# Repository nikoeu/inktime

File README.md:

# Proiect Smartwatch - Documentație Hardware

## 1. Diagramă Bloc

Mai jos este prezentată arhitectura sistemului și modul în care comunică principalele module:

    +-------------------+
    |                   |
    |   BQ25180YBGR     | <==== I2C ====> 
    | (PMIC & Charger)  |                 |
    |                   | --- VREG 3.3V --+
    +-------------------+                 |
                                          |
    +-------------------+                 v
    |                   |
    |                   | <==== I2C ====> IMU (Accel/Gyro)
    |     nRF52840      |
    |  (SoC Principal)  | <==== SPI ====> Ecran E-Paper (EPD)
    |                   |
    |                   | ==== GPIO ====> Driver / Motor Haptic
    +-------------------+

**Conexiuni principale:**

* **Alimentare:** Port USB-C ➜ BQ25180 (PMIC) ➜ Baterie Li-Po & VREG (3.3V System Power). MCU-ul se alimentează din pinul VREG.
* **Periferice I2C:** PMIC-ul (Control/Status) și IMU-ul împart aceeași magistrală I2C.
* **Periferice SPI:** E-Paper Display (EPD) este conectat pe magistrala SPI dedicată.
* **I/O Adițional:** 3 Butoane tactile, Interfața SWD pentru programare și controlul motorului haptic.

## 2. Bill of Materials (BOM)

Tabelul de mai jos conține modulele și componentele principale folosite în designul PCB-ului. Din considerente de formatare pentru recenzie, link-urile directe au fost omise, componentele fiind disponibile standard în catalogul JLC Parts.

| Componentă / Modul | Rol în sistem | Sursă | Documentație |
|---|---|---|---|
| **nRF52840** | Microcontroler principal (BGA) cu BLE | JLC Parts | Datasheet Producător |
| **BQ25180YBGR** | PMIC / Încărcător baterie Li-Po | JLC Parts | Datasheet Producător |
| **LSM6DS3 / MPU6050** | Senzor de mișcare (IMU - Accel/Giroscop) | JLC Parts | Datasheet Producător |
| **Modul EPD SPI** | Conector și suport pentru ecranul E-Paper | JLC Parts | Datasheet Producător |
| **Modul Haptic** | Driver / Motor Vibrații pentru feedback tactil | JLC Parts | Datasheet Producător |
| **Conector USB-C** | Intrare alimentare (VBUS) | JLC Parts | Datasheet Producător |
| **Butoane Tactile SMD** | Interacțiune utilizator (GND pe apăsare) | JLC Parts | Datasheet Producător |

## 3. Descrierea Funcționalității Hardware

Sistemul hardware este proiectat în jurul SoC-ului **nRF52840**, ales pentru capabilitățile sale excelente de Bluetooth Low Energy (BLE) și consumul redus, ideal pentru un dispozitiv purtabil.

* **Managementul Puterii (PMIC):** Am folosit integratul **BQ25180**, un PMIC și încărcător liniar extrem de compact. Acesta preia tensiunea de 5V din portul USB (VBUS), gestionează încărcarea sigură a bateriei (VBAT) și furnizează o tensiune stabilizată sistemului prin pinul VREG/SYS (stabilită la 3.3V). Comunicația cu MCU-ul se face prin magistrala I2C pentru a citi starea bateriei și a configura curentul de încărcare.
* **Interfața cu utilizatorul:** Afișajul este realizat printr-un ecran E-Paper, conectat via magistrala **SPI**. Acest tip de display a fost ales datorită consumului zero de energie pentru reținerea imaginii (esențial pentru autonomia unui ceas). Navigarea se face prin 3 butoane fizice (active low), iar feedback-ul tactil este asigurat de un modul haptic.
* **Senzoristică:** Modulul IMU comunică cu MCU-ul tot prin interfața **I2C** (partajată cu PMIC-ul) și dispune de pini de întrerupere hardware (INT1/INT2) pentru a "trezi" microcontrolerul doar la detectarea mișcării (ex: ridicarea mâinii), economisind astfel baterie.
* **Consum:** În mod *Deep Sleep*, consumul microcontrolerului împreună cu PMIC-ul este de ordinul microamperilor (uA). La activarea BLE și a ecranului (refresh), consumul crește temporar. Sistemul este proiectat astfel încât perifericele să poată fi adormite sau oprite independent.

## 4. Maparea Pinilor nRF52840

Pinii au fost aleși strategic pentru a optimiza rutarea pe PCB sub pachetul BGA, evitând pe cât posibil intersecțiile majore.

| Pin / Label | Funcție asociată | Justificare / Protocol |
|---|---|---|
| **SDA / SCL** | I2C Data & Clock | Magistrala I2C principală. Conectează MCU la BQ25180 și la IMU. |
| **EPD_CS** | Chip Select (Ecran) | Controlează activarea comunicării SPI cu ecranul E-Paper. |
| **EPD_DC** | Data / Command (Ecran) | Indică ecranului dacă datele trimise pe SPI sunt setări sau pixeli. |
| **EPD_RST** | Reset (Ecran) | Reset hardware dedicat pentru inițializarea display-ului. |
| **EPD_BUSY** | Busy State (Ecran) | Intrare în MCU; previne trimiterea de date noi în timp ce ecranul face refresh. |
| **IMU_INT1 / INT2** | Întreruperi Senzor | Trezesc MCU-ul din starea de sleep la detectarea mișcării. |
| **PMIC_INT** | Întrerupere Baterie | Alertează MCU-ul la conectarea cablului USB sau low-battery. |
| **HAPTIC_EN** | Enable Vibrații | Pin GPIO/PWM pentru controlul duratei și intensității vibrațiilor. |
| **RESET** | System Reset | Conectat la pad-urile de test (TP) pentru depanare via SWD. |
| **SWDIO / SWDCLK** | Interfață Programare | Pini dedicați pentru programarea și depanarea nRF52840. |

## 5. Jurnal de Design (Decizii, Probleme și Compromisuri)

Rutarea acestui PCB a reprezentat o provocare majoră din cauza densității mari de componente specifice unui smartwatch și a pachetului BGA al microcontrolerului. Următoarele decizii tehnice au fost luate și asumate pentru a asigura un design funcțional:

1. **Tranziția la un Stack-up cu 4 Straturi (4-Layer PCB):**
   * Datorită aglomerării extreme de pe stratul Top și a numărului mare de airwires rezultate din constrângerile mecanice, am decis utilizarea a 4 straturi.
   * **Layer 2 (Inner 1)** a fost transformat integral într-un plan de masă solid (**GND Polygon Pour**), asigurând ecranare electromagnetică și trasee de întoarcere scurte.
   * **Layer 15 (Inner 2)** a fost utilizat ca plan de alimentare (**3V3 / VREG**), curățând placa de necesitatea rutării zecilor de fire de putere.

2. **Compromisuri acceptate în DRC (Via-in-Pad și Overlap):**
   * **Problemă:** Pinii interni ai microcontrolerului nRF52840 (BGA) erau imposibil de rutat folosind tehnica tradițională ("dog-bone"), spațiul dintre pini fiind insuficient.
   * **Soluție:** Am apelat la tehnica **Via-in-Pad** (Drill: 0.15mm, Annular Ring: 0.075mm pentru a atinge diametrul total de 0.3mm acceptat de fabrica JLC).
   * **Decizie Asumată:** Am acceptat și aprobat manual erorile de tip *Clearance* și *Overlap* generate de soft pe pad-urile BGA-ului, acestea fiind o consecință intenționată (aprobată în prealabil) a utilizării tehnicii Via-in-Pad.

3. **Rutarea firelor de putere prin Vias:**
   * Deși bunele practici recomandă ca traseele de putere principale să fie menținute pe un singur strat continuu pentru a evita rezistența parazită, **am fost nevoit să trag 3 cabluri de putere (grosime 0.3mm) prin vias** pe straturile inferioare. Aglomerarea fizică din jurul zonei PMIC-ului și conectorului USB nu a permis altă soluție de escape routing exclusiv pe stratul TOP.

4. **Amplasarea Antenei (Zona de Restrict):**
   * Antena Bluetooth a fost plasată pe marginea PCB-ului conform cerințelor. Am desenat un decupaj specific în conturul plăcii (Board Outline) și am aplicat reguli de *Keepout* (excludere a poligoanelor de cupru) pe toate cele 4 straturi sub corpul antenei, interzicând rutarea semnalelor pe dedesubt pentru a respecta normele de design RF.

## 6. Limitări curente / Stadiul proiectului

* Designul PCB este complet rutat și trece verificările mecanice principale.
* **Componentă lipsă:** Datorită focusului pe rezolvarea constrângerilor complexe de rutare hardware (BGA + densitate mare de componente) și a timpului alocat asamblării cablajului, **partea de modelare 3D (designul carcasei smartwatch-ului) nu a fost realizată** în acest stadiu al proiectului.

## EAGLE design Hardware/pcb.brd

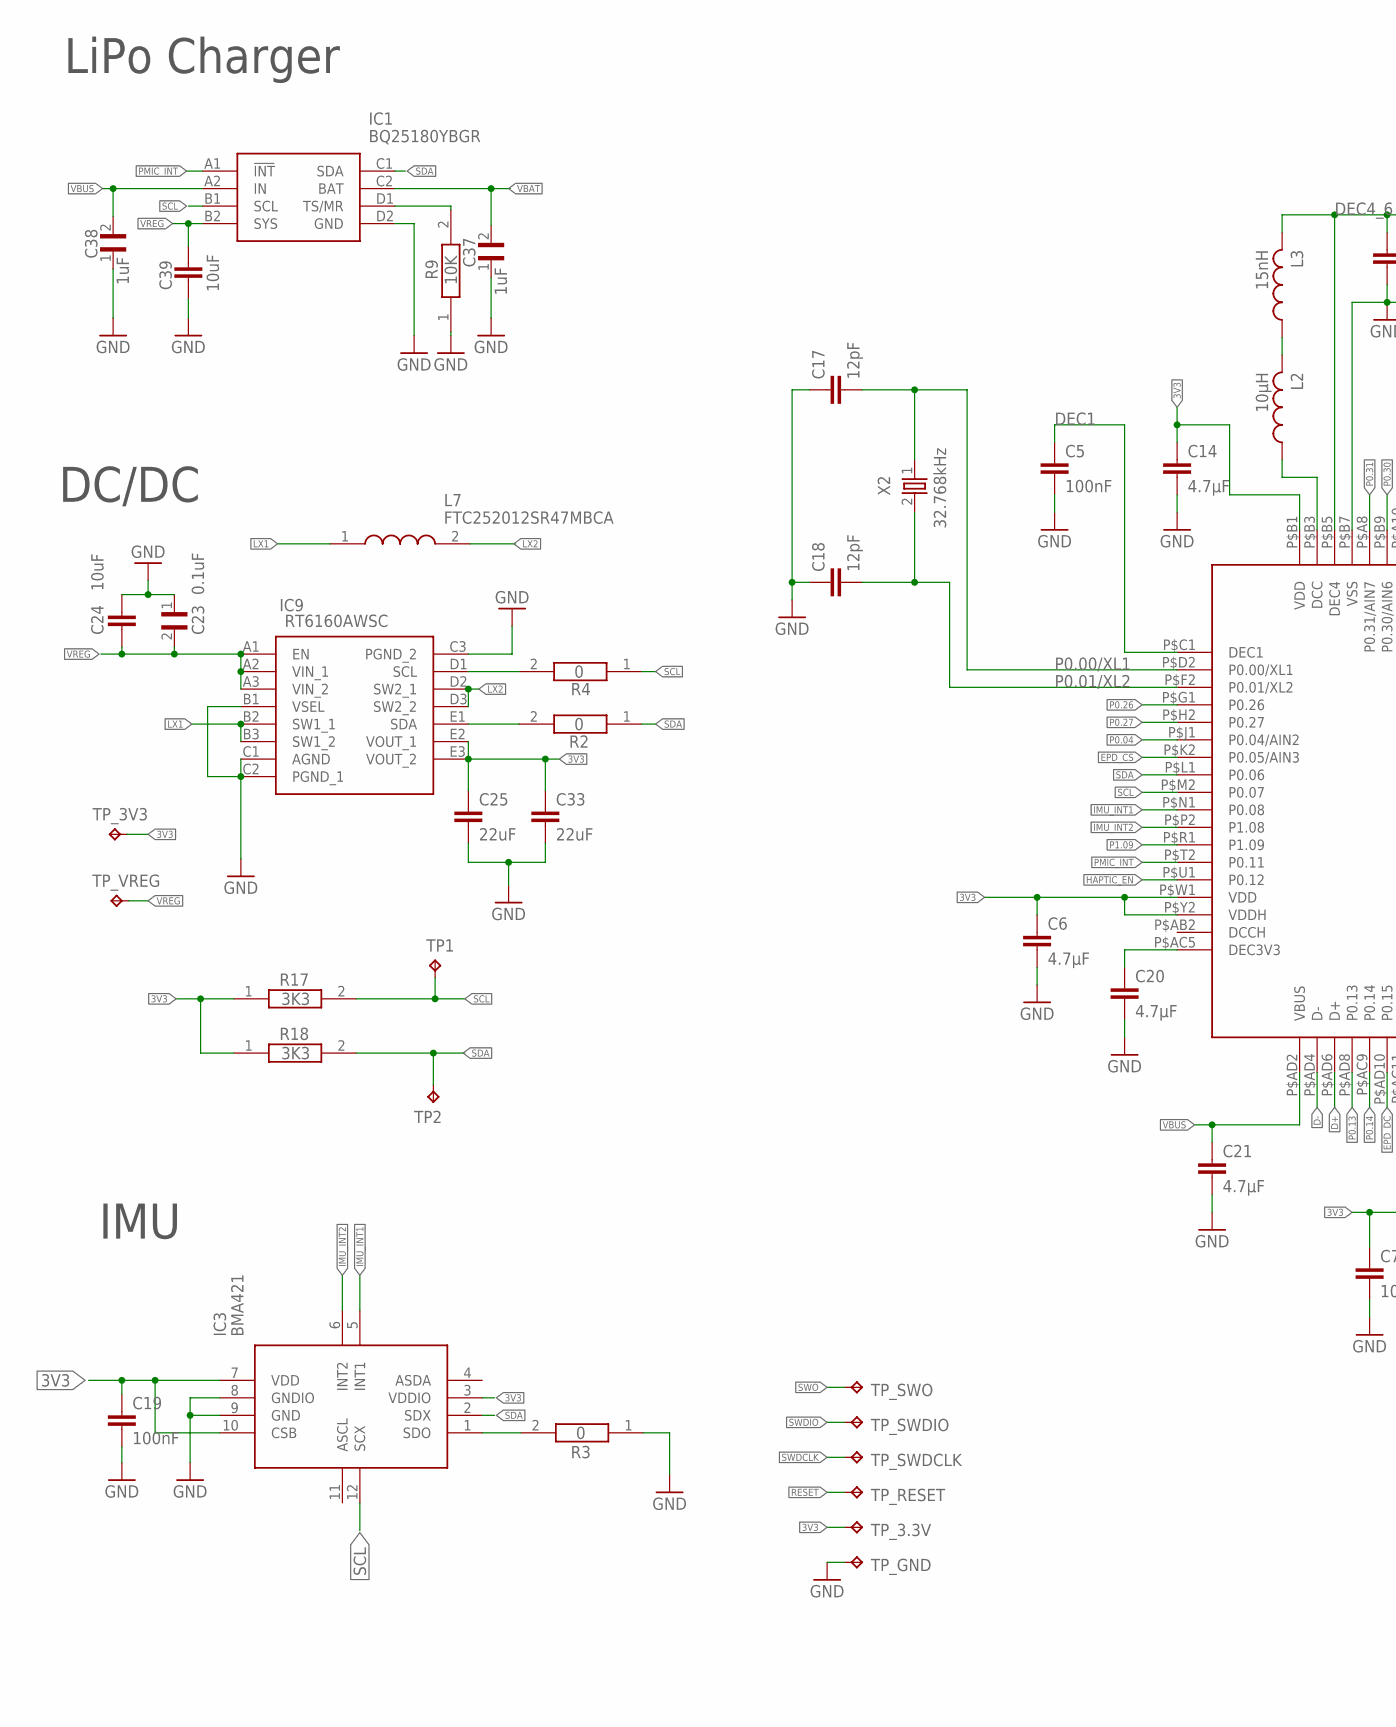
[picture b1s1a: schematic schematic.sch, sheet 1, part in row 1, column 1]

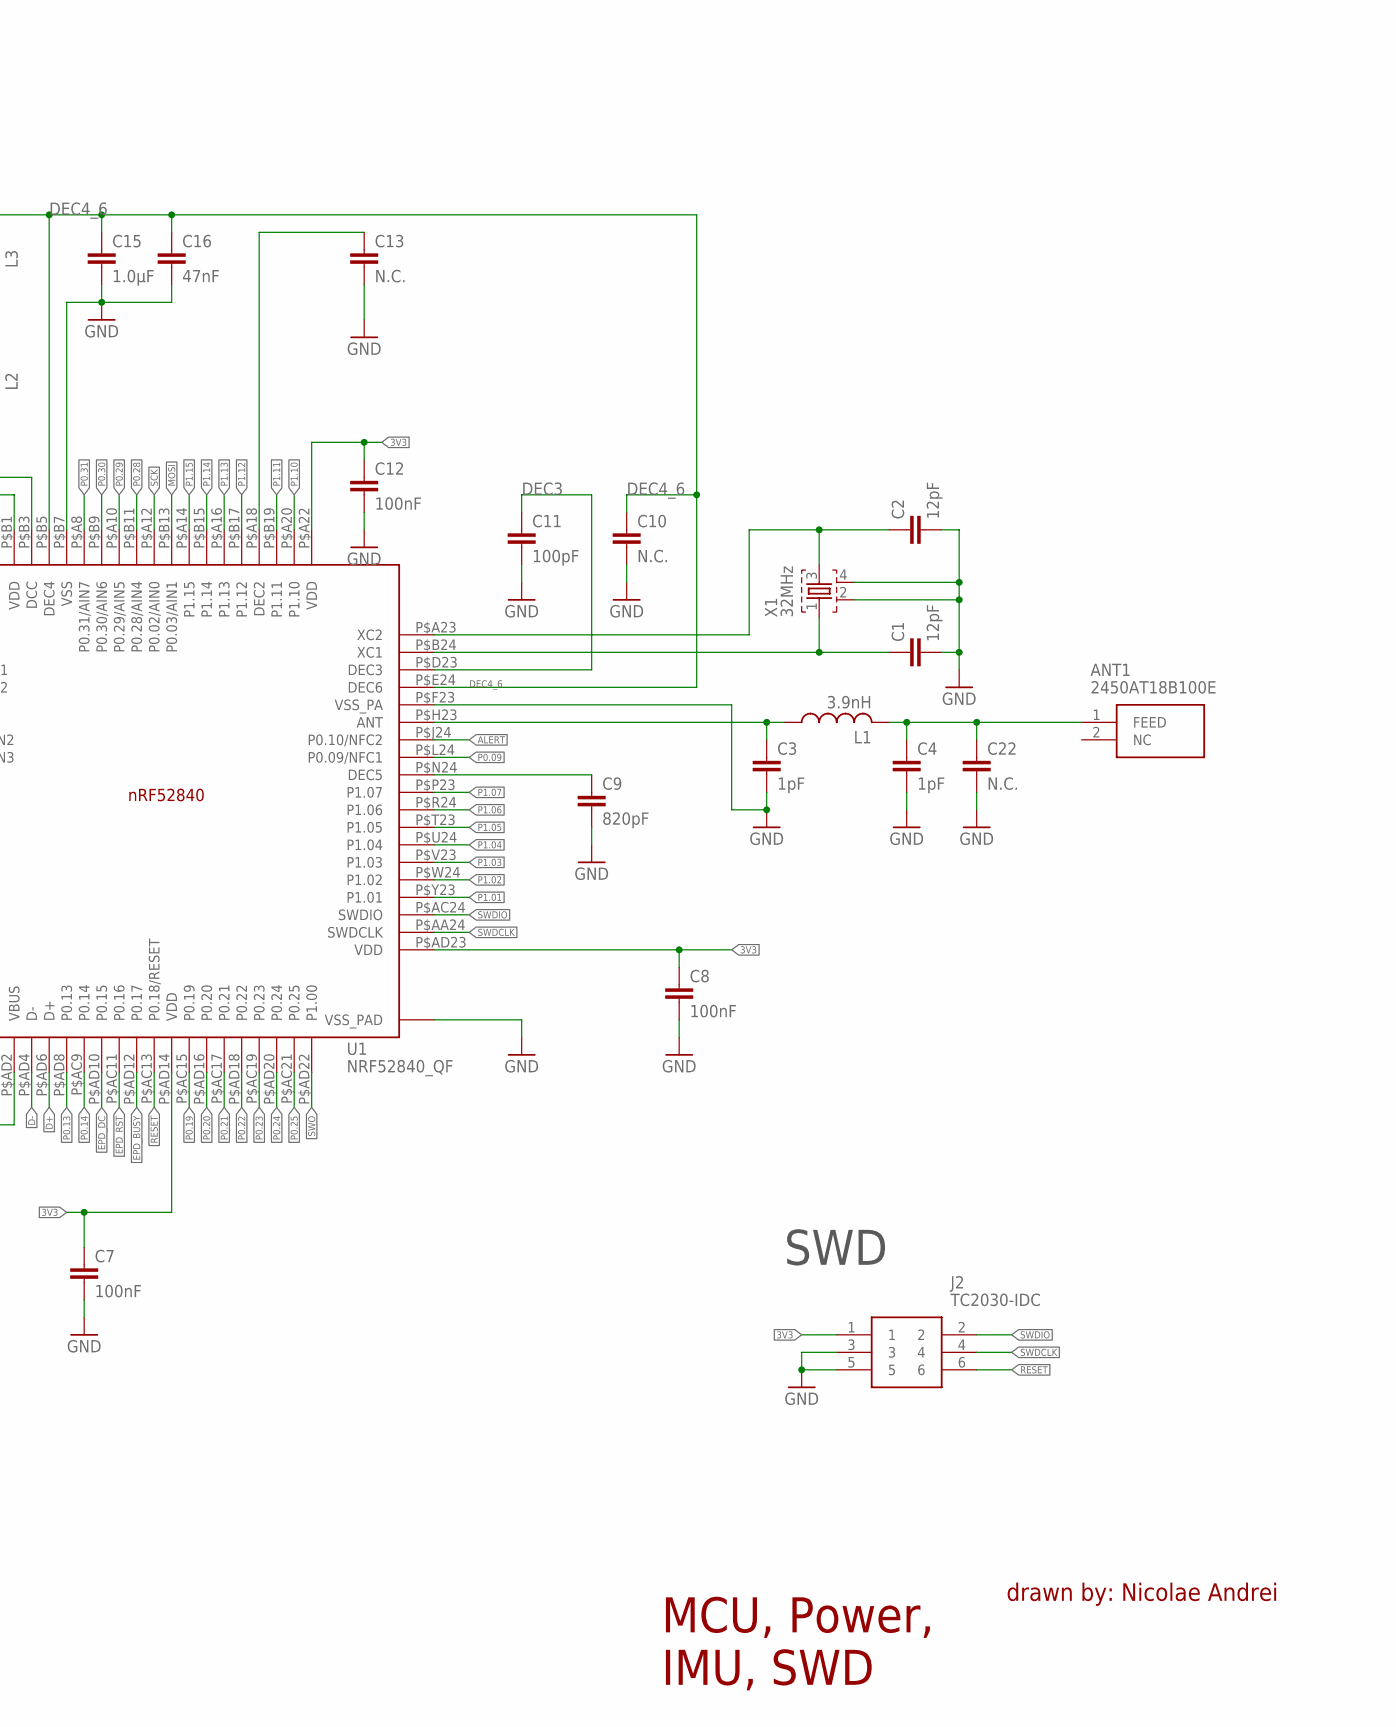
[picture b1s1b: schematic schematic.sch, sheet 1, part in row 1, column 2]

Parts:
ANT1: 2450AT18B100E; 2450AT18B100E_ANTC3216X140N
C1, C2, C17, C18: 12pF; NORDIC_NRF_3_RESC0201_L
C3, C4: 1pF; NORDIC_NRF_3_RESC0201_L
C5, C7, C8, C12, C19: 100nF; NORDIC_NRF_3_RESC0201_L
C6, C14, C20, C21: 4.7μF; NORDIC_NRF_3_RESC0402_L
C9: 820pF; NORDIC_NRF_3_RESC0201_L
C10, C13, C22: N.C.; NORDIC_NRF_3_RESC0201_L
C11: 100pF; NORDIC_NRF_3_RESC0201_L
C15: 1.0μF; NORDIC_NRF_3_RESC0402_L
C16: 47nF; NORDIC_NRF_3_RESC0201_L
C23: 0.1uF; GRM011R60J152KE01L_1_0201
C24, C39: 10uF; PERFECT_0402_0402
C25, C33: 22uF; PERFECT_0402_0402
C37, C38: 1uF; GRM011R60J152KE01L_1_0201
IC1: BQ25180YBGR; BQ25180YBGR_BGA8C40P2X4_100X155X50
IC3: BMA421; BMA423_BMA423
IC9: RT6160AWSC; RT6160AWSC_BGA15C40P3X5_140X230X60
J2: TC2030-IDC; TC2030-IDC_TC2030IDC
L1: 3.9nH; NORDIC_NRF_2_RESC0402_L
L2: 10μH; NORDIC_NRF_2_RESC0402_L
L3: 15nH; NORDIC_NRF_2_RESC0402_L
L7: FTC252012SR47MBCA; MLP2016SR47MT0S1_INDC2016X100N
R2, R3, R4: 0; CPF0201D7K68C1_0201
R9: 10K; CPF0201D7K68C1_0201
R17, R18: 3K3; CPF0201D7K68C1_0201
TP1, TP2: HECTOR_WATCH_1_TPTP20R; HECTOR_WATCH_1_TP20R
TP_3.3V, TP_3V3: HECTOR_WATCH_1_TPTP20R; HECTOR_WATCH_1_TP20R
TP_GND: HECTOR_WATCH_1_TPTP20R; HECTOR_WATCH_1_TP20R
TP_RESET: HECTOR_WATCH_1_TPTP20R; HECTOR_WATCH_1_TP20R
TP_SWDCLK: HECTOR_WATCH_1_TPTP20R; HECTOR_WATCH_1_TP20R
TP_SWDIO: HECTOR_WATCH_1_TPTP20R; HECTOR_WATCH_1_TP20R
TP_SWO: HECTOR_WATCH_1_TPTP20R; HECTOR_WATCH_1_TP20R
TP_VREG: HECTOR_WATCH_1_TPTP20R; HECTOR_WATCH_1_TP20R
U1: NRF52840_QF; NORDIC_NRF_4_AQFN50P700X700X85_HS-74N
X1: 32MHz; NORDIC_NRF_BT-XTAL_2016_N
X2: 32.768kHz; NORDIC_NRF_1_XTAL_3215_N

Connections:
3V3: C6.1, C7.1, C8.1, C12.1, C14.1, C19.1, C25.1, C33.1, IC3.3 (VDDIO), IC3.7 (VDD), IC3.10 (CSB), IC9.E2 (VOUT_1), IC9.E3 (VOUT_2), J2.1, R17.1, R18.1, TP_3.3V.TP, TP_3V3.TP, U1.P$A22 (VDD), U1.P$AD14 (VDD), U1.P$AD23 (VDD), U1.P$B1 (VDD), U1.P$W1 (VDD), U1.P$Y2 (VDDH); also elsewhere on the board
ALERT: U1.P$J24 (P0.10/NFC2); also elsewhere on the board
D+: U1.P$AD6 (D+); also elsewhere on the board
D-: U1.P$AD4 (D-); also elsewhere on the board
DEC1: C5.1, U1.P$C1 (DEC1)
DEC3: C11.1, U1.P$D23 (DEC3)
DEC4_6: C10.1, C15.1, C16.1, L3.2, U1.P$B5 (DEC4), U1.P$E24 (DEC6)
EPD_BUSY: U1.P$AD12 (P0.17); also elsewhere on the board
EPD_CS: U1.P$K2 (P0.05/AIN3); also elsewhere on the board
EPD_DC: U1.P$AD10 (P0.15); also elsewhere on the board
EPD_RST: U1.P$AC11 (P0.16); also elsewhere on the board
GND: C1.2, C2.2, C3.2, C4.2, C5.2, C6.2, C7.2, C8.2, C9.2, C10.2, C11.2, C12.2, C13.2, C14.2, C15.2, C16.2, C17.1, C18.1, C19.2, C20.2, C21.2, C22.2, C23.1, C24.1, C25.2, C33.2, C37.1, C38.1, C39.2, IC1.D2 (GND), IC3.8 (GNDIO), IC3.9 (GND), IC9.B1 (VSEL), IC9.C1 (AGND), IC9.C2 (PGND_1), IC9.C3 (PGND_2), J2.3, J2.5, R3.1, R9.1, TP_GND.TP, U1.P$74 (VSS_PAD), U1.P$75 (VSS_PAD), U1.P$76 (VSS_PAD), U1.P$77 (VSS_PAD), U1.P$78 (VSS_PAD), U1.P$79 (VSS_PAD), U1.P$80 (VSS_PAD), U1.P$81 (VSS_PAD), U1.P$82 (VSS_PAD), U1.P$83 (VSS_PAD), U1.P$84 (VSS_PAD), U1.P$85 (VSS_PAD), U1.P$86 (VSS_PAD), U1.P$87 (VSS_PAD), U1.P$88 (VSS_PAD), U1.P$89 (VSS_PAD), U1.P$90 (VSS_PAD), U1.P$B7 (VSS), U1.P$F23 (VSS_PA), X1.2, X1.4; also elsewhere on the board
HAPTIC_EN: U1.P$U1 (P0.12); also elsewhere on the board
IMU_INT1: IC3.5 (INT1), U1.P$N1 (P0.08)
IMU_INT2: IC3.6 (INT2), U1.P$P2 (P1.08)
LX1: IC9.B2 (SW1_1), IC9.B3 (SW1_2), L7.1
LX2: IC9.D2 (SW2_1), IC9.D3 (SW2_2), L7.2
MOSI: U1.P$B13 (P0.03/AIN1); also elsewhere on the board
unnamed: IC1.D1 (TS/MR), R9.2
unnamed: IC9.D1 (SCL), R4.2
unnamed: IC9.E1 (SDA), R2.2
unnamed: IC3.1 (SDO), R3.2
unnamed: L2.1, U1.P$B3 (DCC)
unnamed: L2.2, L3.1
unnamed: C2.1, U1.P$A23 (XC2), X1.3
unnamed: C13.1, U1.P$A18 (DEC2)
unnamed: C1.1, U1.P$B24 (XC1), X1.1
unnamed: C3.1, L1.1, U1.P$H23 (ANT)
unnamed: ANT1.1 (FEED), C4.1, C22.1, L1.2
unnamed: C9.1, U1.P$N24 (DEC5)
unnamed: C20.1, U1.P$AC5 (DEC3V3)
P0.00/XL1: C17.2, U1.P$D2 (P0.00/XL1), X2.1
P0.01/XL2: C18.2, U1.P$F2 (P0.01/XL2), X2.2
P0.04: U1.P$J1 (P0.04/AIN2)
P0.09: U1.P$L24 (P0.09/NFC1)
P0.13: U1.P$AD8 (P0.13); also elsewhere on the board
P0.14: U1.P$AC9 (P0.14); also elsewhere on the board
P0.19: U1.P$AC15 (P0.19)
P0.20: U1.P$AD16 (P0.20)
P0.21: U1.P$AC17 (P0.21)
P0.22: U1.P$AD18 (P0.22)
P0.23: U1.P$AC19 (P0.23)
P0.24: U1.P$AD20 (P0.24)
P0.25: U1.P$AC21 (P0.25)
P0.26: U1.P$G1 (P0.26)
P0.27: U1.P$H2 (P0.27)
P0.28: U1.P$B11 (P0.28/AIN4)
P0.29: U1.P$A10 (P0.29/AIN5)
P0.30: U1.P$B9 (P0.30/AIN6)
P0.31: U1.P$A8 (P0.31/AIN7)
P1.01: U1.P$Y23 (P1.01); also elsewhere on the board
P1.02: U1.P$W24 (P1.02); also elsewhere on the board
P1.03: U1.P$V23 (P1.03)
P1.04: U1.P$U24 (P1.04)
P1.05: U1.P$T23 (P1.05)
P1.06: U1.P$R24 (P1.06)
P1.07: U1.P$P23 (P1.07)
P1.09: U1.P$R1 (P1.09)
P1.10: U1.P$A20 (P1.10)
P1.11: U1.P$B19 (P1.11)
P1.12: U1.P$B17 (P1.12)
P1.13: U1.P$A16 (P1.13)
P1.14: U1.P$B15 (P1.14)
P1.15: U1.P$A14 (P1.15)
PMIC_INT: IC1.A1 (!INT), U1.P$T2 (P0.11)
RESET: J2.6, TP_RESET.TP, U1.P$AC13 (P0.18/RESET)
SCK: U1.P$A12 (P0.02/AIN0); also elsewhere on the board
SCL: IC1.B1 (SCL), IC3.12 (SCX), R4.1, R17.2, TP1.TP, U1.P$M2 (P0.07); also elsewhere on the board
SDA: IC1.C1 (SDA), IC3.2 (SDX), R2.1, R18.2, TP2.TP, U1.P$L1 (P0.06); also elsewhere on the board
SWDCLK: J2.4, TP_SWDCLK.TP, U1.P$AA24 (SWDCLK)
SWDIO: J2.2, TP_SWDIO.TP, U1.P$AC24 (SWDIO)
SWO: TP_SWO.TP, U1.P$AD22 (P1.00)
VBAT: C37.2, IC1.C2 (BAT); also elsewhere on the board
VBUS: C21.1, C38.2, IC1.A2 (IN), U1.P$AD2 (VBUS); also elsewhere on the board
VREG: C23.2, C24.2, C39.1, IC1.B2 (SYS), IC9.A1 (EN), IC9.A2 (VIN_1), IC9.A3 (VIN_2), TP_VREG.TP

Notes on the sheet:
LiPo Charger
DC/DC
IMU
SWD
MCU, Power, IMU, SWD
drawn by: Nicolae Andrei

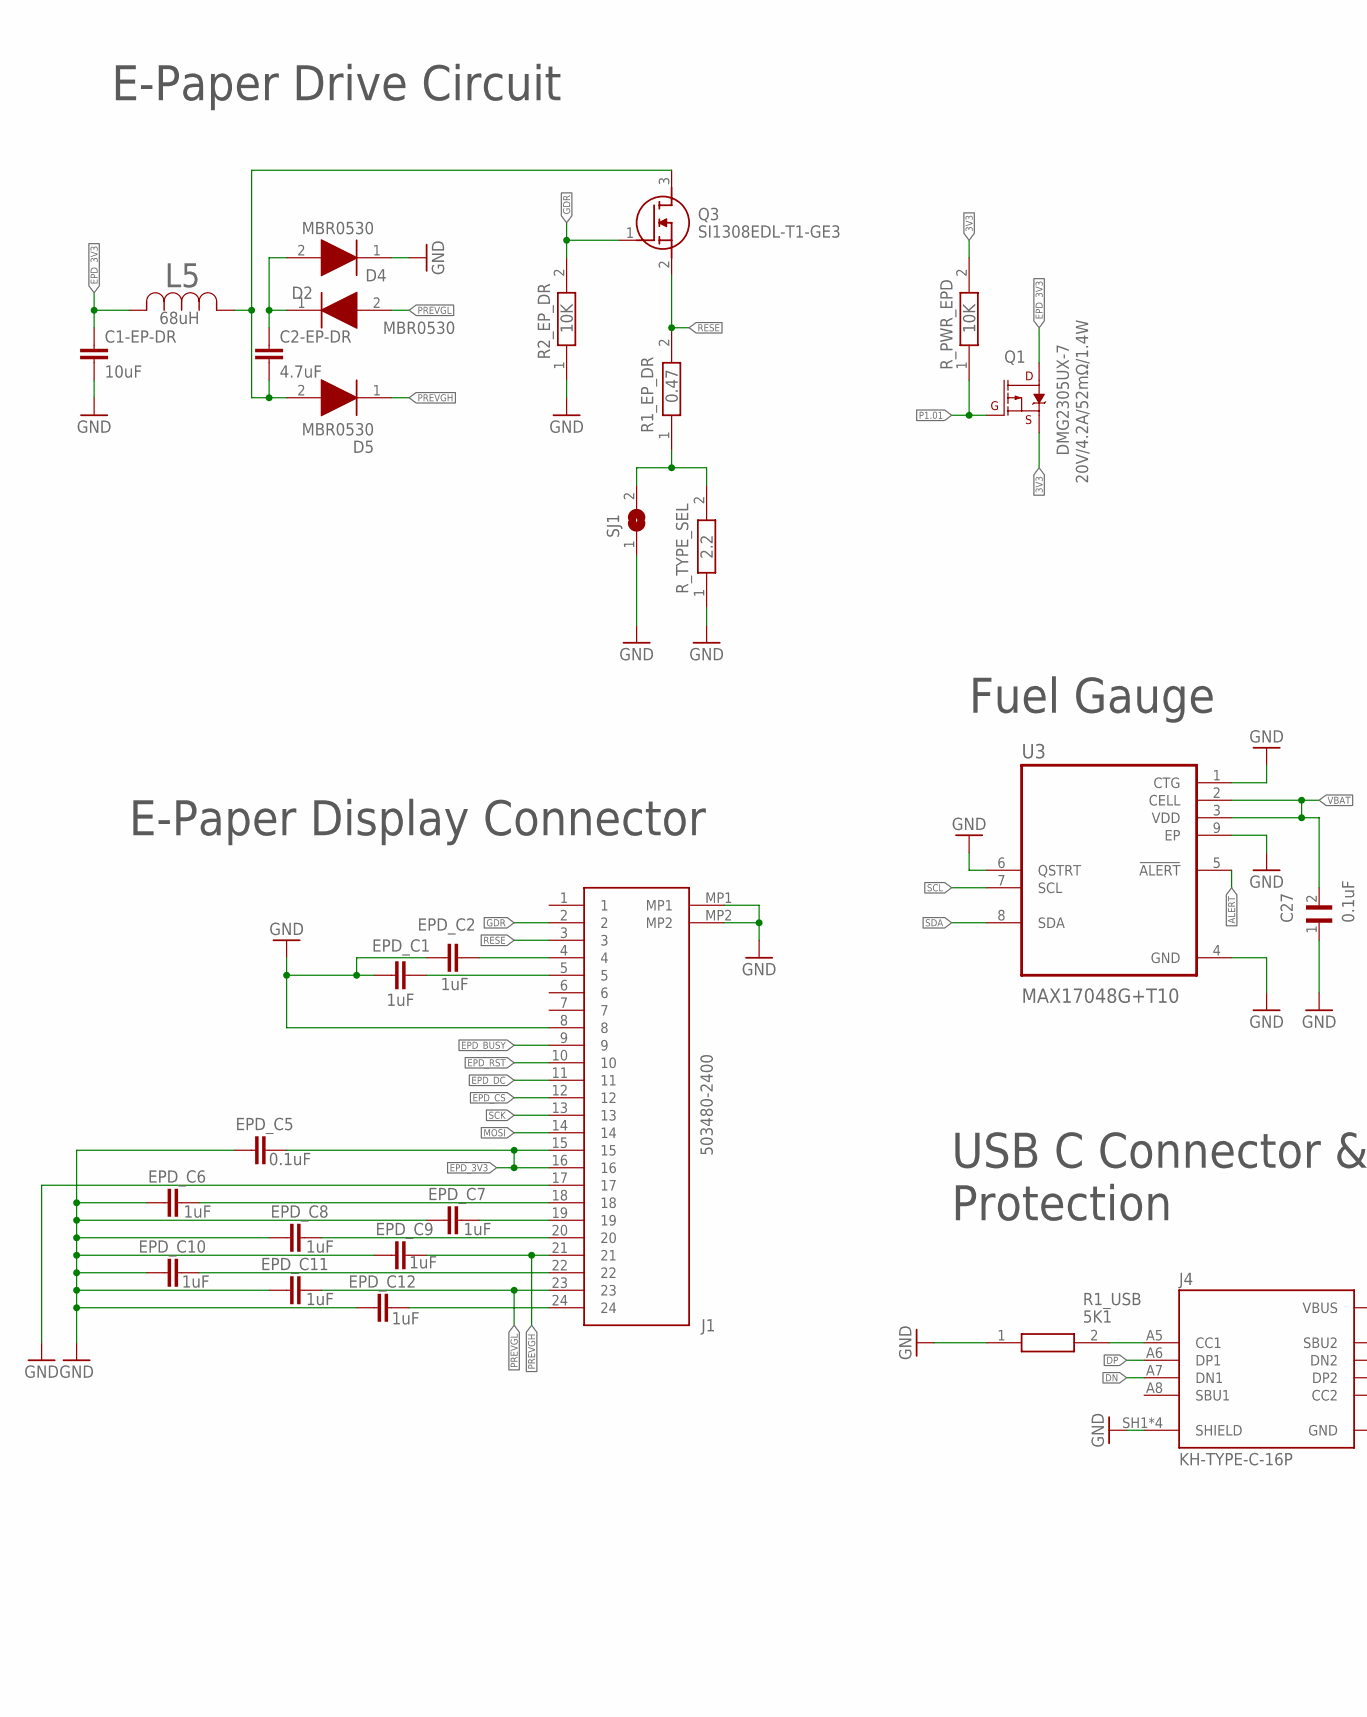
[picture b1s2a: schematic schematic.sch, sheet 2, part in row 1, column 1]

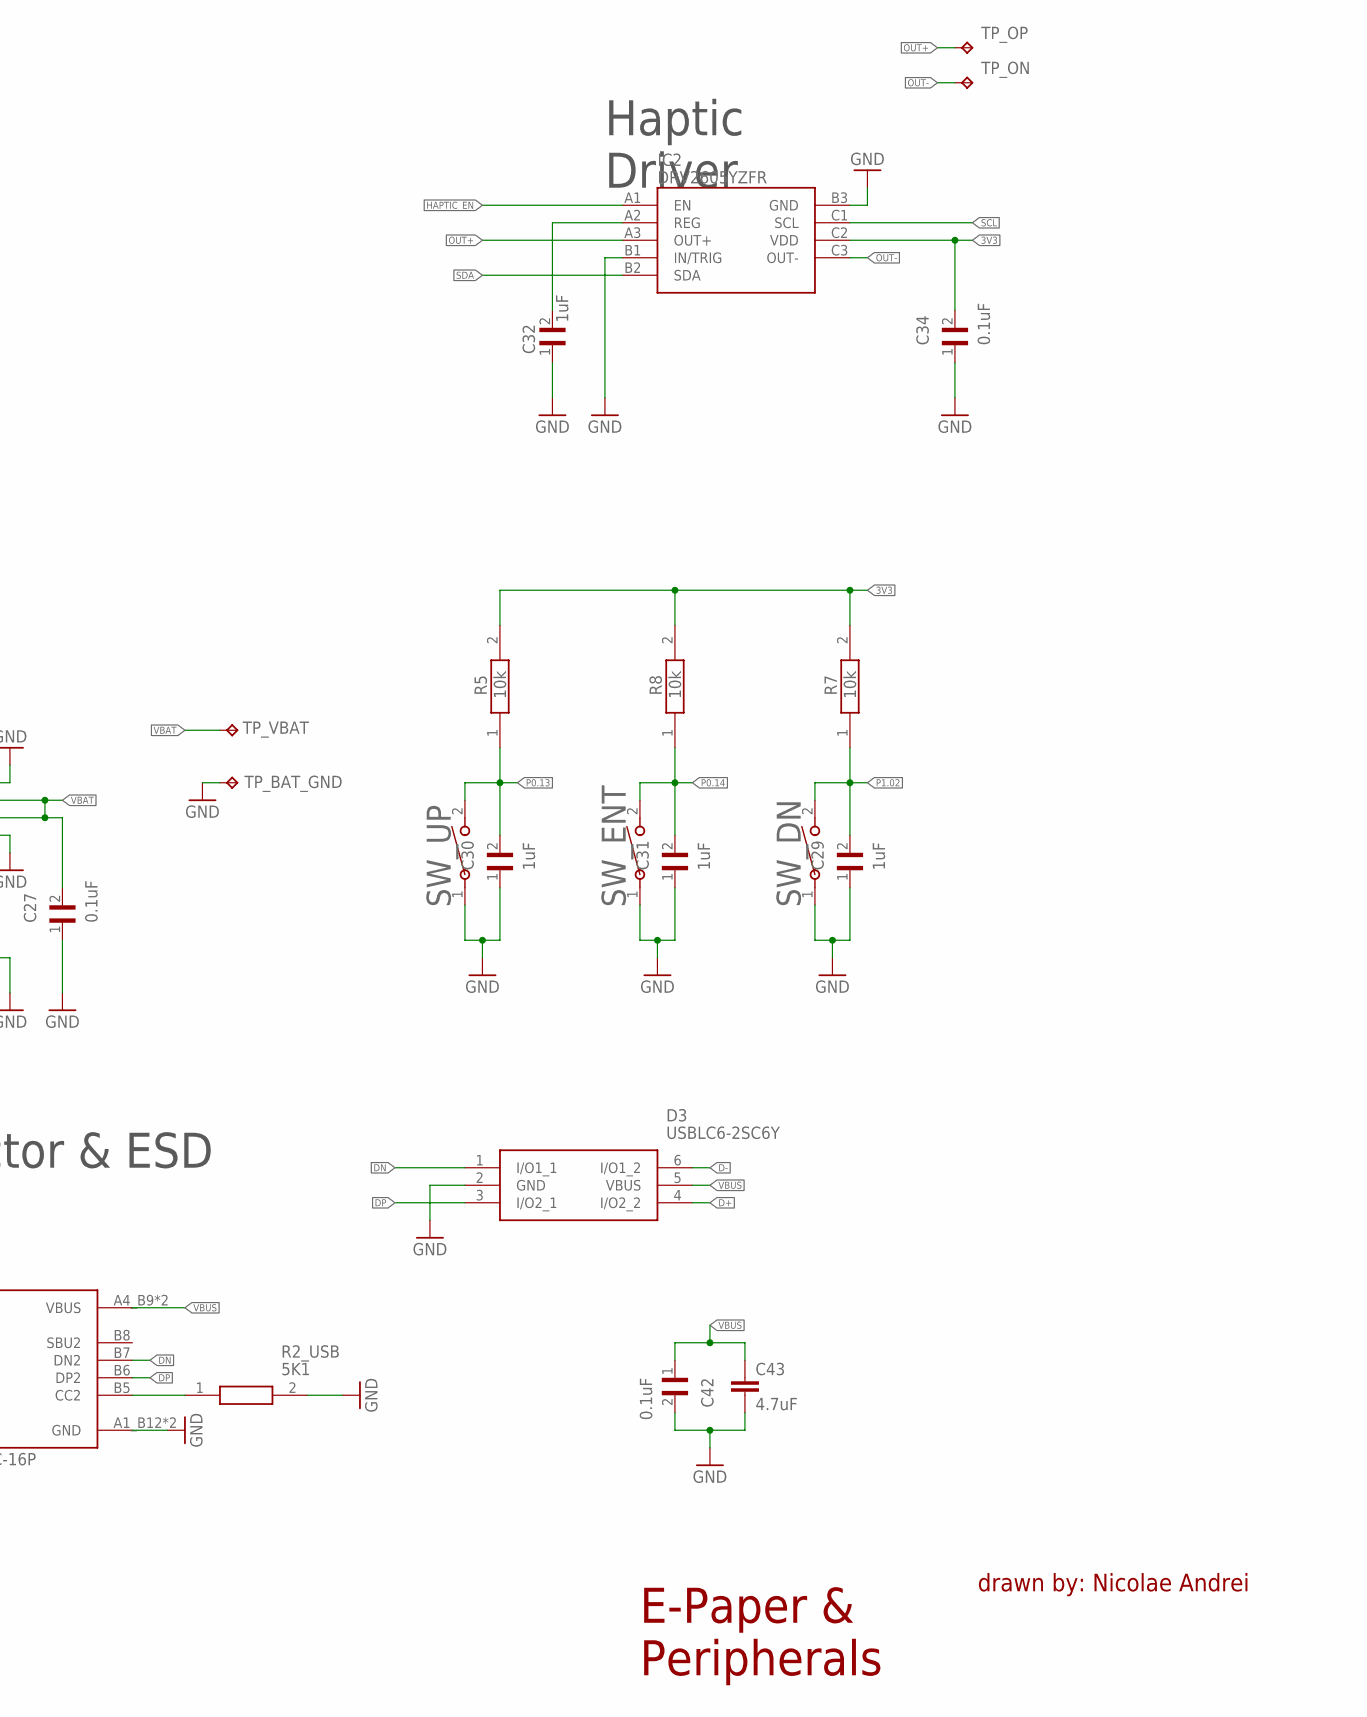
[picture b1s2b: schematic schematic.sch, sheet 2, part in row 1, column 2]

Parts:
C1-EP-DR: 10uF; ESP32_C6_LIBRARY_1_ESP32_WROVER_EAGLE-LTSPICE_C0402
C2-EP-DR: 4.7uF; ESP32_C6_LIBRARY_1_ESP32_WROVER_EAGLE-LTSPICE_C0402
C27, C34, C42: 0.1uF; GRM011R60J152KE01L_2_CAPC0201X13N
C29, C30, C31, C32: 1uF; GRM011R60J152KE01L_2_CAPC0201X13N
C43: 4.7uF; NORDIC_NRF_3_RESC0402_L
D2, D4, D5: MBR0530; ESP32_C6_LIBRARY_5_SOD3716X135N
D3: USBLC6-2SC6Y; ESP32_C6_LIBRARY_3_SOT95P280X145-6N
EPD_C1, EPD_C2, EPD_C6, EPD_C7, EPD_C8, EPD_C9, EPD_C10, EPD_C11, EPD_C12: 1uF; ESP32_C6_LIBRARY_1_ESP32_WROVER_EAGLE-LTSPICE_C0402
EPD_C5: 0.1uF; ESP32_C6_LIBRARY_1_ESP32_WROVER_EAGLE-LTSPICE_C0402
IC2: DRV2605YZFR; DRV2605YZFR_BGA9C50P3X3_144X144X62
J1: 503480-2400; 503480-2400_5034802400
J4: KH-TYPE-C-16P; KH-TYPE-C-16P_KINGHELM_KH-TYPE-C-16P
L5: 68uH; ESP32_C6_LIBRARY_2_IND_4828-WE-TPC_WRE
Q1: 20V/4.2A/52mΩ/1.4W; ESP32_C6_LIBRARY_4_ESP32_C6_LIBRARY_4_ESP32_C6_LIBRARY_4_ES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
Q3: SI1308EDL-T1-GE3; ESP32_C6_LIBRARY_6_SOT65P210X110-3N
R1_EP_DR: 0.47; CPF0201D7K68C1_0201
R1_USB, R2_USB: 5K1; CPF0201D7K68C1_0201
R2_EP_DR: 10K; CPF0201D7K68C1_0201
R5, R7, R8: 10k; CPF0201D7K68C1_0201
R_PWR_EPD: 10K; CPF0201D7K68C1_0201
R_TYPE_SEL: 2.2; CPF0201D7K68C1_0201
SJ1: ESP32_C6_LIBRARY_7_JUMPER_SJ
SW_DN: 2025-10-22_07-23-44_LIBRARY_EVP-AKE31ASW_EVP-AKE3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; 2025-10-22_07-23-44_LIBRARY_SW_EVP-AKE31A_PAN
SW_ENT: 2025-10-22_07-23-44_LIBRARY_EVP-AKE31ASW_EVP-AKE3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; 2025-10-22_07-23-44_LIBRARY_SW_EVP-AKE31A_PAN
SW_UP: 2025-10-22_07-23-44_LIBRARY_EVP-AKE31ASW_EVP-AKE3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; 2025-10-22_07-23-44_LIBRARY_SW_EVP-AKE31A_PAN
TP_BAT_GND: HECTOR_WATCH_1_TPTP20R; HECTOR_WATCH_1_TP20R
TP_ON: HECTOR_WATCH_1_TPTP20R; HECTOR_WATCH_1_TP20R
TP_OP: HECTOR_WATCH_1_TPTP20R; HECTOR_WATCH_1_TP20R
TP_VBAT: HECTOR_WATCH_1_TPTP20R; HECTOR_WATCH_1_TP20R
U3: MAX17048G+T10; ESP32_C6_LIBRARY_SON50P200X200X80-9N

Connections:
3V3: C34.2, IC2.C2 (VDD), Q1.2 (S), R5.2, R7.2, R8.2, R_PWR_EPD.2; also elsewhere on the board
ALERT: U3.5 (!ALERT); also elsewhere on the board
D+: D3.4 (I/O2_2); also elsewhere on the board
D-: D3.6 (I/O1_2); also elsewhere on the board
DN: D3.1 (I/O1_1), J4.A7 (DN1), J4.B7 (DN2)
DP: D3.3 (I/O2_1), J4.A6 (DP1), J4.B6 (DP2)
EPD_3V3: C1-EP-DR.1, EPD_C5.2, J1.15, J1.16, L5.2, Q1.3 (D)
EPD_BUSY: J1.9; also elsewhere on the board
EPD_CS: J1.12; also elsewhere on the board
EPD_DC: J1.11; also elsewhere on the board
EPD_RST: J1.10; also elsewhere on the board
GDR: J1.2, Q3.1 (G), R2_EP_DR.2
GND: C1-EP-DR.2, C27.1, C29.1, C30.1, C31.1, C32.1, C34.1, C42.2, C43.2, D2.1 (K), D3.2 (GND), EPD_C1.1, EPD_C2.1, EPD_C5.1, EPD_C6.1, EPD_C7.1, EPD_C8.1, EPD_C9.1, EPD_C10.1, EPD_C11.1, EPD_C12.1, IC2.B1 (IN/TRIG), IC2.B3 (GND), J1.8, J1.17, J1.MP1, J1.MP2, J4.A1_B12 (GND), J4.A12_B1 (GND), J4.SH1 (SHIELD), J4.SH2 (SHIELD), J4.SH3 (SHIELD), J4.SH4 (SHIELD), R1_USB.1, R2_EP_DR.1, R2_USB.2, R_TYPE_SEL.1, SJ1.1, SW_DN.1, SW_ENT.1, SW_UP.1, TP_BAT_GND.TP, U3.1 (CTG), U3.4 (GND), U3.6 (QSTRT), U3.9 (EP); also elsewhere on the board
HAPTIC_EN: IC2.A1 (EN); also elsewhere on the board
MOSI: J1.14; also elsewhere on the board
unnamed: C2-EP-DR.2, D5.2 (A), L5.1, Q3.3 (D)
unnamed: C2-EP-DR.1, D2.2 (A), D4.1 (K)
unnamed: R1_EP_DR.1, R_TYPE_SEL.2, SJ1.2
unnamed: EPD_C2.2, J1.4
unnamed: EPD_C12.2, J1.24
unnamed: C32.2, IC2.A2 (REG)
unnamed: EPD_C10.2, J1.22
unnamed: EPD_C8.2, J1.20
unnamed: EPD_C7.2, J1.19
unnamed: EPD_C6.2, J1.18
unnamed: EPD_C1.2, J1.5
unnamed: J4.A5 (CC1), R1_USB.2
unnamed: J4.B5 (CC2), R2_USB.1
OUT+: IC2.A3 (OUT+), TP_OP.TP
OUT-: IC2.C3 (OUT-), TP_ON.TP
P0.13: C30.2, R5.1, SW_UP.2; also elsewhere on the board
P0.14: C31.2, R8.1, SW_ENT.2; also elsewhere on the board
P1.01: Q1.1 (G), R_PWR_EPD.1; also elsewhere on the board
P1.02: C29.2, R7.1, SW_DN.2; also elsewhere on the board
PREVGH: D5.1 (K), EPD_C9.2, J1.21
PREVGL: D4.2 (A), EPD_C11.2, J1.23
RESE: J1.3, Q3.2 (S), R1_EP_DR.2
SCK: J1.13; also elsewhere on the board
SCL: IC2.C1 (SCL), U3.7 (SCL); also elsewhere on the board
SDA: IC2.B2 (SDA), U3.8 (SDA); also elsewhere on the board
VBAT: C27.2, TP_VBAT.TP, U3.2 (CELL), U3.3 (VDD); also elsewhere on the board
VBUS: C42.1, C43.1, D3.5 (VBUS), J4.A4_B9 (VBUS), J4.A9_B4 (VBUS); also elsewhere on the board

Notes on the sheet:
E-Paper Drive Circuit
E-Paper Display Connector
Fuel Gauge
USB C Connector & ESD Protection
Haptic Driver
E-Paper & Peripherals
drawn by: Nicolae Andrei

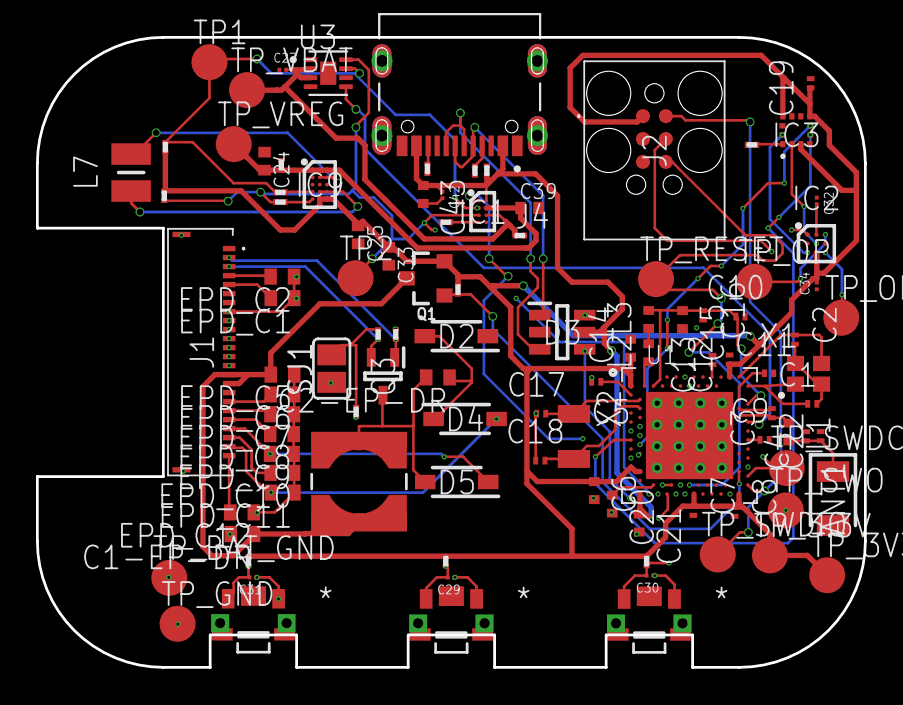
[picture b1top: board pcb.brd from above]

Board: 4 copper layers, 46.0 x 35.0 mm, 105 parts (0 on the bottom side), 70 nets.

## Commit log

2026-04-22 Add hardware documentation for smartwatch project
    Added detailed hardware documentation for the smartwatch project, including block diagrams, BOM, functionality descriptions, pin mapping, design journal, and current limitations.
2026-04-22 Create temp

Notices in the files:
parts and their libraries:
COPYRIGHT: Copyright (C) 2024 Ultra Librarian. All rights reserved.
COPYRIGHT: Copyright (C) 2025 Ultra Librarian. All rights reserved.
